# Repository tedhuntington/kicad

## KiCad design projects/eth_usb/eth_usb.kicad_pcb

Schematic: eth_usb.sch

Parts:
C1, C8, C10, C11, C12: 0.1uF
C2: 1uF
C3, C4, C19, C20: 18pF
C5, C6, C13, C16, C18, C21: .1uF
C7, C9, C15: 4.7uF
C14: 10uF
C17: .47uF
FB1: 500mA
J1: HEADER_6X1
J2: HEADER_9X2
J3: Logic DC_2.1MM; TED_DC_2.1mm
J4: USB
J5: HEADER_7X2
R1, R2, R3, R6, R7, R8: 33
R4: 12.1k 1%
R5: 1M
R9, R10, R11, R12: 49.9
R13, R15: 255
R14: 4.7k
R16: 10k 1%
U1: RJ45_12_PIN
U2: LAN8720A/LAN8720AI; QFN24
U3: REGULATOR_3.3V
U4: PIC32MX664F064H; TED_TQFP64
X1: 25 MHz
X2: 8Mhz

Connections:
+3.3v: C5.1, C6.1, C8.1, C9.1, C10.1, C11.1, C12.1, C18.1, C21.1, FB1.1, J1.2, J2.10, J5.8, R9.1, R10.1, R11.1, R12.1, R14.1, U1.4 (CT), U1.5 (CT), U2.9, U3.2, U4.10 (VDD), U4.19 (AVDD), U4.26 (VDD), U4.35 (VUSB3V3), U4.38 (VDD), U4.57 (VDD)
+5v_Vbus: C15.1, C17.1, J2.11, J3.1, J4.1 (+5V), J5.9, U3.3, U4.34 (VBUS)
AVDD: FB1.2, U2.1, U2.19
D+: J4.3 (D+), U4.37 (D+/RG2)
D-: J4.2 (D-), U4.36 (D-/RG3)
ECRSDV: R8.2, U4.62 (ERXDV/ECRSDV/PMD2/RE2)
EMDC: U2.13, U4.30 (AN15/EMDC/AEMDC/OCFB/PMALL/PMA0/CN12/RB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)
EMDIO: U2.12, U4.49 (EMDIO/AEMDIO/SCK3/U4TX/~U1RTS~/OC2/RD1)
EREFCLK: U2.14, U4.63 (ERXCLK/EREFCLK/PMD3/RE3)
ERXD0: R7.2, U4.61 (ERXD0/PMD1/RE1)
ERXD1: R6.2, U4.60 (ERXD1/PMD0/RE0)
ERXERR: U2.10, U4.64 (ERXERR/PMD4/RE4)
ETXD0: R2.2, U4.2 (ETXD0/PMD6/RE6)
ETXD1: R3.2, U4.3 (ETXD1/PMD7/RE7)
ETXEN: R1.2, U4.1 (ETXEN/PMD5/RE5)
GND: C1.2, C2.2, C3.1, C4.1, C5.2, C6.2, C8.2, C9.2, C10.2, C11.2, C12.2, C13.2, C14.2, C15.2, C16.2, C17.2, C18.2, C19.2, C20.2, C21.2, J1.3, J2.9, J3.2, J4.4 (GND), J5.7, R4.2, R16.2, U1.8 (CHS_GROUND), U1.10 (GreenLED-), U1.12 (YellowLED-), U2.25, U3.1, U4.9 (VSS), U4.20 (AVSS), U4.25 (VSS), U4.41 (VSS)
GreenLED: R15.1, U1.9 (GreenLED+)
ICSPCLK_RB1: J1.5, J2.18, U4.15 (PGEC1/AN1/VREF-/CVREF-/CN3/RB1)
ICSPDAT_RB0: J1.4, J2.1, U4.16 (PGED1/AN0/VREF+/CVREF+/PMA6/CN2/RB0)
unnamed: R13.2, U2.3
unnamed: R15.2, R16.1, U2.2
unnamed: C3.2, R5.1, U2.5, X1.1
unnamed: R4.1, U2.24
unnamed: R7.1, U2.8
unnamed: R6.1, U2.7
unnamed: C4.2, R5.2, U2.4, X1.2
unnamed: C1.1, C2.1, U2.6
unnamed: C13.1, C14.1, U4.56 (VCAP)
unnamed: C19.1, U4.40 (OSC2/CLKO/RC15), X2.1
unnamed: R8.1, U2.11
unnamed: R3.1, U2.18
unnamed: R2.1, U2.17
unnamed: R1.1, U2.16
unnamed: C16.1, J4.5 (SHELL)
unnamed: C20.1, U4.39 (OSC1/CLKI/RC12), X2.2
RB2: J2.2, U4.14 (AN2/C2IN-/CN4/RB2)
RB3: J2.17, U4.13 (AN3/C2IN+/CN5/RB3)
RB4: J2.3, U4.12 (AN4/C1IN-/CN6/RB4)
RB5: J2.16, U4.11 (AN5/C1IN+/VBUSON/CN7/RB5)
RB6: J2.4, U4.17 (PGEC2/AN6/OCFA/RB6)
RB7: J2.15, U4.18 (PGED2/AN7/RB7)
RB8: J2.5, U4.21 (AN8/~SS4~/U5RX/~U2CTS~/C1OUT/RB8)
RB9: J2.14, U4.22 (AN9/C2OUT/PMA7/RB9)
RB10: J2.6, U4.23 (TMS/AN10/CVREFOUT/PMA13/RB10)
RB11: J2.13, U4.24 (TDO/AN11/PMA12/RB11)
RB12: J2.7, U4.27 (TCK/AN12/PMA11/RB12)
RB13: J2.12, U4.28 (TDI/AN13/PMA10/RB13)
RB14: J2.8, U4.29 (AN14/SCK4/U5TX/~U2RTS~/PMALH/PMA1/RB14)
RD0: J5.1, U4.46 (OC1/INT0/RD0)
RD2: J5.14, U4.50 (SDA3/SDI3/U1RX/OC3/RD2)
RD3: J5.2, U4.51 (SCL3/SDO3/U1TX/OC4/RD3)
RD4: J5.13, U4.52 (OC5/IC5/PMWR/CN13/RD4)
RD5: J5.3, U4.53 (PMRD/CN14/RD5)
RD6: J5.12, U4.54 (AETXEN/ETXERR/CN15/RD6)
RD7: J5.4, U4.55 (ETXCLK/AERXERR/CN16/RD7)
RD8: J5.11, U4.42 (RTCC/AERXD1/ETXD3/IC1/INT1/RD8)
RD9: J5.5, U4.43 (AERXD0/ETXD2/~SS3~/U4RX/~U1CTS~/SDA1/IC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)
RD10: J5.10, U4.44 (ECOL/AECRSDV/SCL1/IC3/PMCS2/PMA15/INT3/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)
RD11: J5.6, U4.45 (ECRS/AEREFCLK/IC4/PMCS1/PMA14/INT4/RD11)
RXN: R9.2, U1.6 (RD-), U2.22
RXP: R10.2, U1.3 (RD+), U2.23
TXN: R11.2, U1.2 (TD-), U2.20
TXP: R12.2, U1.1 (TD+), U2.21
YellowLED: R13.1, U1.11 (YellowLED+)
nRST: U2.15, U4.58 (AETXD1/ERXD3/RF0)
~MCLR~: J1.1, R14.2, U4.7 (~MCLR~)

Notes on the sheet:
Ethernet = 100Mbps (10ns/bit), SPI = 25Mbps (40ns/bit)
PRG/DBG ICSP 90 DEGREE HEADER
PCB uses all SMT except RJ45
SS4 Note: slave select SPI support is disabled.
Note: With Ethernet, only two SPI buses are possible (SPI2 and SPI4)
note: later may want to add secondary clock (32.768 khz) to save power when not in use
Probably SPI2 will be later used as a second SPI bus for sensors
VUSB3V3: USB internal transceiver supply. If the USB module is not used, this pin must be connected to VDD.
Yellow=Link/Action
Green=Bus Speed 100Mbit=lit
PORT B (MALE)
PORT D (MALE)

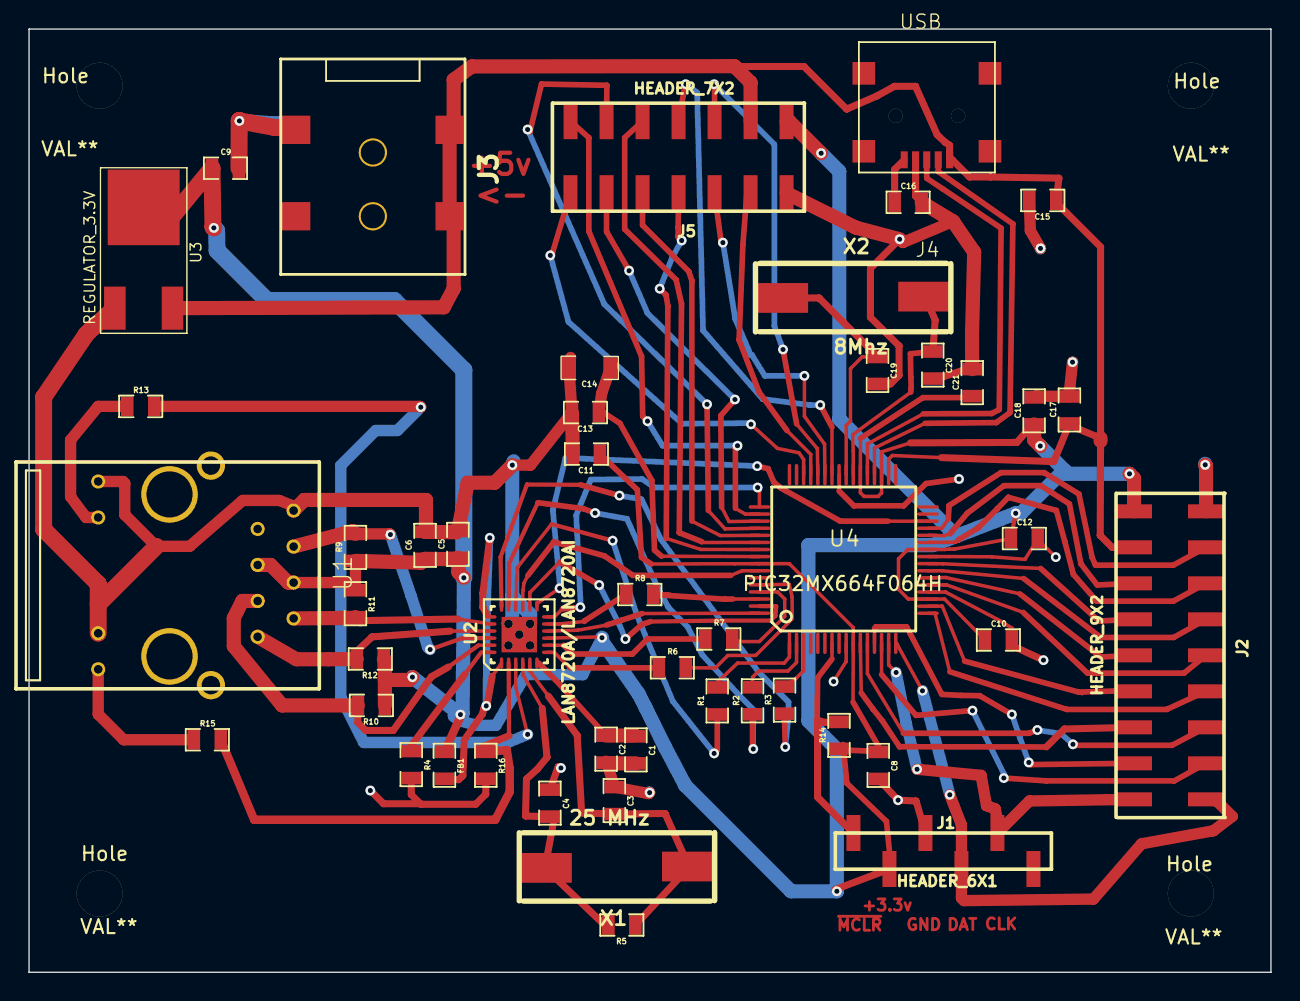
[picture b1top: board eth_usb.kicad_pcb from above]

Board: 2 copper layers, 87.6 x 66.6 mm, 52 parts (0 on the bottom side), 66 nets.

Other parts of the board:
Hole: VAL**; TED_Hole_3.25mm
Hole#2, Hole#3, Hole#4: VAL**; TED_Hole_3.25mm

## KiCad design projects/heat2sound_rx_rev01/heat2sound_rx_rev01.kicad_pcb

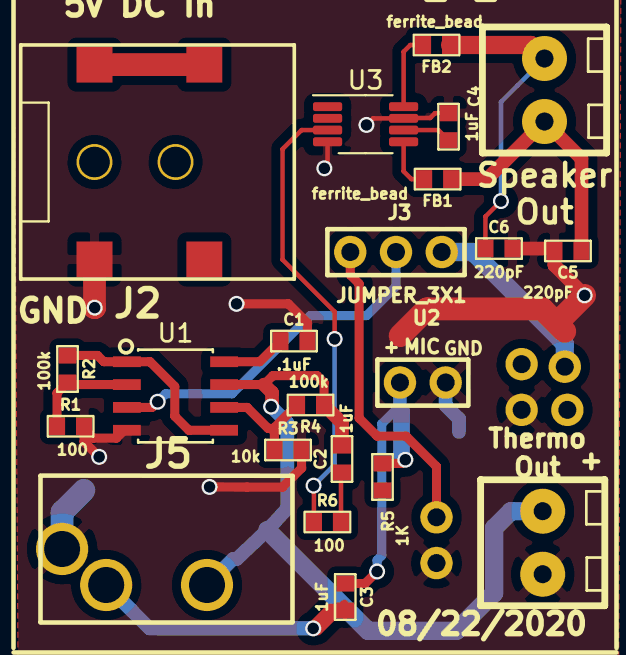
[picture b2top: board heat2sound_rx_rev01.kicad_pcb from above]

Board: 2 copper layers, 24 parts (0 on the bottom side), 18 nets.

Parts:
C1: .1uF; TED_SM0603_C
C2, C3, C4: 1uF; TED_SM0603_C
C5, C6: 220pF; TED_SM0603_C
FB1, FB2: ferrite_bead; TED_SM0603_R
J1: TERMINAL_3.5MM_PCB_2PIN; TED_HEADER_2x1
J2: DC_2.1mm; TED_2.1mm_DC_SMD
J3: JUMPER_3X1; TED_HEADER_3x1
J4, J6: TERMINAL_3.5MM_PCB_2PIN; TED_TERMINAL_3.5MM_2PIN
J5: 3.5_STEREO; TED_3.5_Stereo_STX-3150-3N-1
R1, R6: 100; TED_SM0603_R
R2, R4: 100k; TED_SM0603_R
R3: 10k; TED_SM0603_R
R5: 1K; TED_SM0603_R
S1: THERMOPILE_MLX90247; TED_HEADER_2x2_THERMO
U1: MCP6V02; SOIC-8
U2: MIC; TED_HEADER_2x1
U3: PAM8302A; MSOP-8_3x3mm_P0.65mm

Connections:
GND: C1.2, C4.2, C5.2, C6.2, J1.1, J2.2, J4.2, J5.1, R1.2, R3.2, S1.3, U1.4, U2.2, U3.4, U3.7
unnamed: C1.1, U1.8
unnamed: C2.1, R6.2
unnamed: C2.2, J4.1, J5.2, R4.1, U1.7
unnamed: C3.1, R5.2, U2.1
unnamed: C3.2, J5.3
unnamed: C4.1, U3.6
unnamed: C5.1, FB1.1, J6.2
unnamed: C6.1, FB2.1, J6.1
unnamed: FB1.2, U3.5
unnamed: FB2.2, U3.8
unnamed: J1.2, J3.1
unnamed: J3.2, U1.3
unnamed: J3.3, S1.1
unnamed: R1.1, R2.2, U1.2
unnamed: R2.1, U1.1, U1.5
unnamed: R3.1, R4.2, U1.6
unnamed: R6.1, U3.3
